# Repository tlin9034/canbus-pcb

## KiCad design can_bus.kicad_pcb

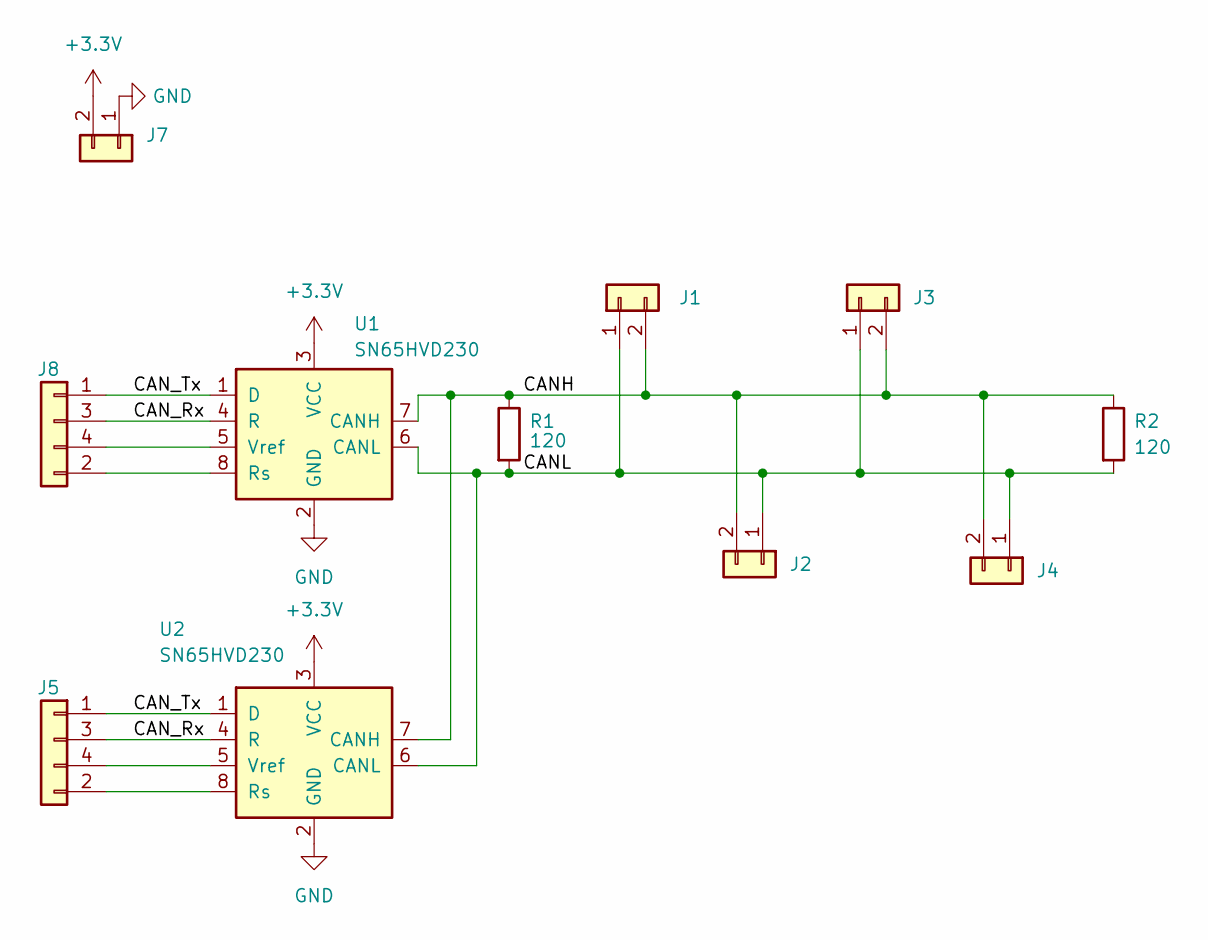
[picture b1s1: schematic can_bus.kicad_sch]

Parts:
J1, J2, J3, J4, J7: Conn_01x02; TerminalBlock_Phoenix_MPT-0,5-2-2.54_1x02_P2.54mm_Horizontal
J5, J8: Conn_01x04; TerminalBlock_Phoenix_MPT-0,5-4-2.54_1x04_P2.54mm_Horizontal
R1, R2: 120; R_0805_2012Metric_Pad1.20x1.40mm_HandSolder
U1, U2: SN65HVD230; SOIC-8_3.9x4.9mm_P1.27mm

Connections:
+3.3V: J7.2, U1.3 (VCC), U2.3 (VCC)
/CANH: J1.2, J2.2, J3.2, J4.2, R1.1, R2.1, U1.7 (CANH), U2.7 (CANH)
/CANL: J1.1, J2.1, J3.1, J4.1, R1.2, R2.2, U1.6 (CANL), U2.6 (CANL)
/CAN_Rx: J5.3, J8.3, U1.4 (R), U2.4 (R)
/CAN_Tx: J5.1, J8.1, U1.1 (D), U2.1 (D)
GND: J7.1, U1.2 (GND), U2.2 (GND)
unnamed: J5.2, U2.8 (Rs)
unnamed: J5.4, U2.5 (Vref)
unnamed: J8.2, U1.8 (Rs)
unnamed: J8.4, U1.5 (Vref)

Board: 2 copper layers, 11 parts (0 on the bottom side), 10 nets, no tracks yet.

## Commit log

2024-03-04 Initial commit: Adding KiCad project files
